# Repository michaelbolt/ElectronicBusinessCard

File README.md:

# ElectronicBusinessCard
This repository contains the code and PCB design files I developed for my Electronic Business Card project. To see writeups and follow my progress, follow my blog: [Mr. Dr. Prof. Bolt](https://mrdrprofbolt.wordpress.com/).

### Current State of the Project: Finished!
The MSP430FR2433 microcontroller communicates with the SSD1306 OLED display through I2C and handles 8x8 sprite-based animations. A Python GUI is available to help with creating animated sprite data. GPIO Port 2 is debounced using a polling algorithm for player input. A basic game loop implementing player controls (verical movement and lasers), enemy AI (vertical/horizontal movement and lasers), and collision detection (explosions!) is run at 16 Hz using the TimerA module and Low-Power Mode 3. Three different enemies are implemented along with collision detection and a score counter, with life-time high score stored in non-volatile FRAM. If the player gets a high score, a fireworks show is shown to celebrate!

### Using the Sprite Maker GUI
1. Download the `SpriteMaker.py` file from the `PythonScripts` folder.
2. Navigte to the directory where the source file is located. Use `cd [folder name]` to navigate on Mac/Linux or `DIR [folder name]` to navigate on Windows.
3. Run the script from the command line as `python SpriteMaker.py`. If you would like to see command line options, add the `-h` option.
4. Enjoy!

### Using the SSD1306 display functions
1. At the start of each frame, call `display_frameStart()`; this erases anything drawn on the last frame from VRAM.
2. Draw up to 16 sprites at (x,y) coordinates with `display_drawSprite(uint16_t x, uint16_t y, const uint8_t *const sprite)`.
3. After drawing all sprites, call `display_drawFrame()`; this updates all changed regions of the SSD1306 display with minimal I2C communication.

### Board Design files
Open in Eagle, edit the silkscreen to show your name, and go forth! Impress job interviewers, your friends, and anybody sitting next to you while waiting for a table at a restaurant!

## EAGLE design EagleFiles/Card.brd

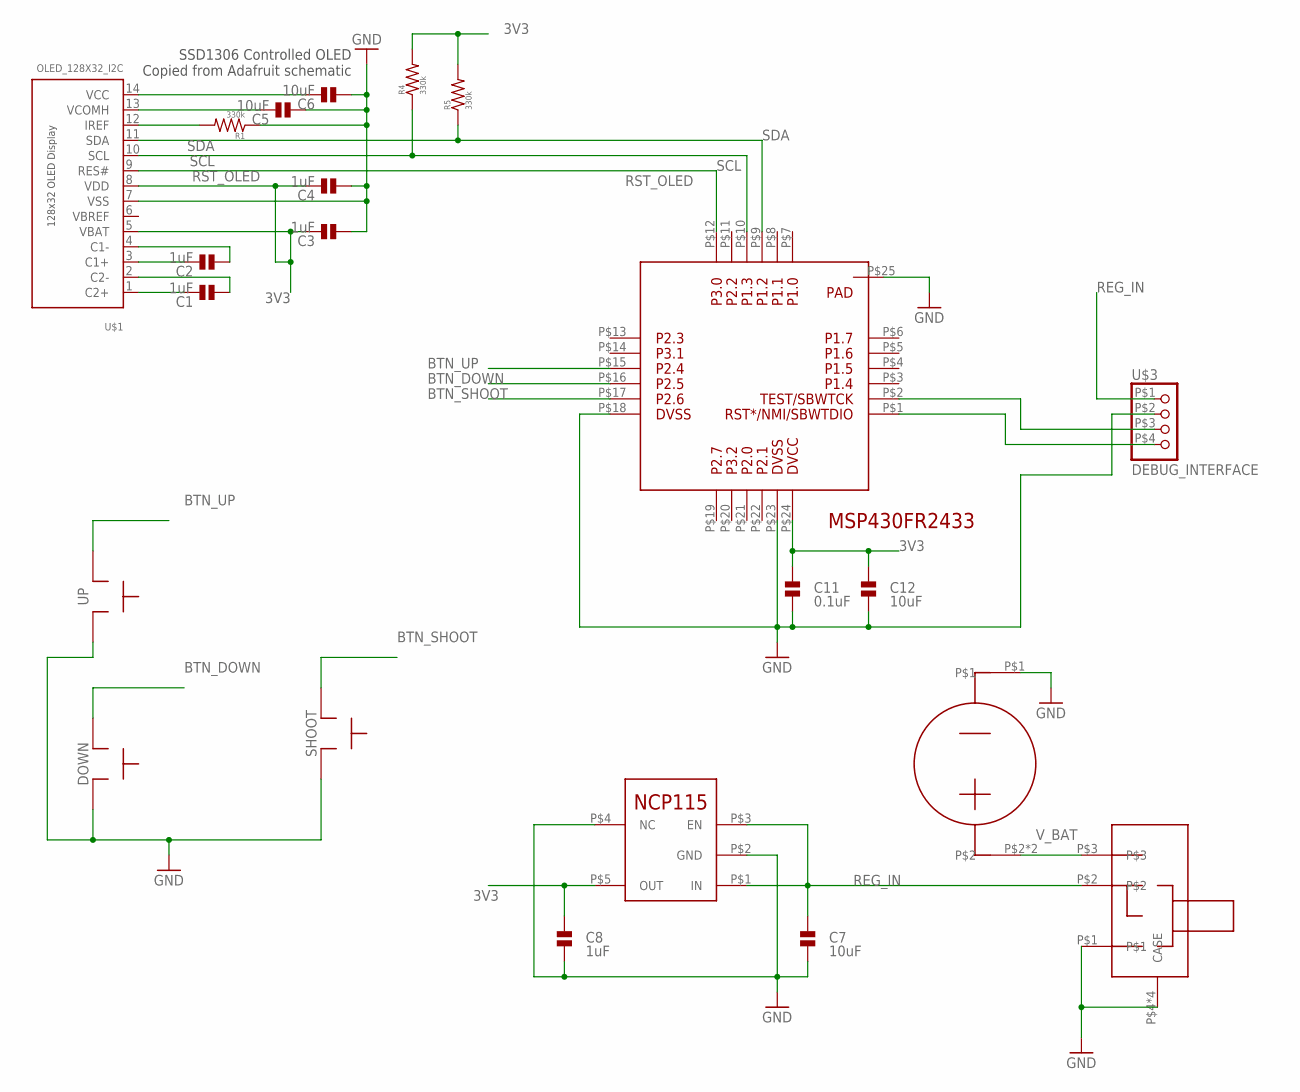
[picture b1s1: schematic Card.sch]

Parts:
C1, C2, C3, C4, C8: 1uF; 0603
C5, C6, C7, C12: 10uF; 0603
C11: 0.1uF; 0603
DOWN: EVQ-Q2B02W; EVQQ2
R1, R4, R5: 330k; 0603
SHOOT: EVQ-Q2B02W; EVQQ2
U$1: OLED_128X32_I2C; OLED_I2C
U$2: MSP430FR2433-VQFN; VQFN-24
U$3: DEBUG_INTERFACE; DEBUG_INTERFACE_6PIN
U$4: BAT-HLD-001
U$5: CUS-12TB; CUS-12B
U$6: NCP115; TSOP-5
UP: EVQ-Q2B02W; EVQQ2

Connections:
3V3: C3.2, C4.2, C8.2, C11.2, C12.2, R4.2, R5.2, U$1.5 (VBAT), U$1.8 (VDD), U$2.P$24, U$6.P$5 (OUT)
BTN_DOWN: DOWN.P$1_A, DOWN.P$2_A, U$2.P$16
BTN_SHOOT: SHOOT.P$1_A, SHOOT.P$2_A, U$2.P$17
BTN_UP: U$2.P$15, UP.P$1_A, UP.P$2_A
GND: C3.1, C4.1, C5.1, C6.1, C7.1, C8.1, C11.1, C12.1, DOWN.P$3_B, DOWN.P$4_B, R1.1, SHOOT.P$3_B, SHOOT.P$4_B, U$1.7 (VSS), U$2.P$18, U$2.P$23, U$2.P$25, U$3.P$2, U$4.P$1, U$5.P$1, U$5.P$4 (CASE), U$5.P$5 (CASE), U$5.P$6 (CASE), U$5.P$7 (CASE), U$6.P$2 (GND), U$6.P$4 (NC), UP.P$3_B, UP.P$4_B
unnamed: C1.2, U$1.1 (C2+)
unnamed: C1.1, U$1.2 (C2-)
unnamed: C2.2, U$1.3 (C1+)
unnamed: C2.1, U$1.4 (C1-)
unnamed: U$2.P$2, U$3.P$3
unnamed: U$2.P$1, U$3.P$4
unnamed: R1.2, U$1.12 (IREF)
unnamed: C5.2, U$1.13 (VCOMH)
unnamed: C6.2, U$1.14 (VCC)
REG_IN: C7.2, U$3.P$1, U$5.P$2, U$6.P$1 (IN), U$6.P$3 (EN)
RST_OLED: U$1.9 (RES#), U$2.P$12
SCL: R4.1, U$1.10 (SCL), U$2.P$10
SDA: R5.1, U$1.11 (SDA), U$2.P$9
VBREF: U$1.6 (VBREF)
V_BAT: U$4.P$2, U$4.P$3, U$5.P$3

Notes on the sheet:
SSD1306 Controlled OLED Copied from Adafruit schematic

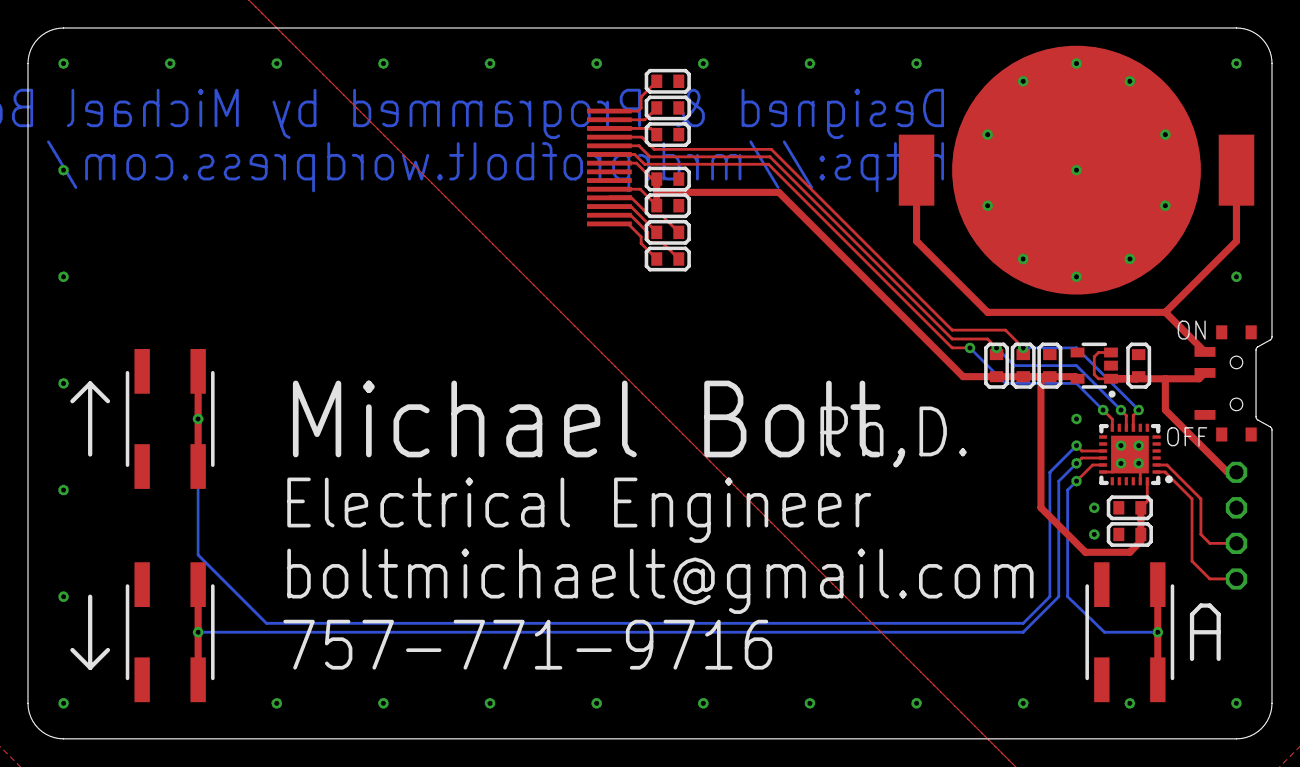
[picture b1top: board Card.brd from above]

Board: 2 copper layers, 88.9 x 50.8 mm, 22 parts (0 on the bottom side), 19 nets.

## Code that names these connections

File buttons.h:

/*
 * buttons.h
 *
 *  Created on: May 4, 2020
 *      Author: Michael Bolt
 */

#ifndef BUTTONS_H_
#define BUTTONS_H_


#include <msp430.h>
#include <stdint.h>

// button definitions
#define BTN_UP      BIT2
#define BTN_DOWN    BIT1
#define BTN_SHOOT   BIT0

// functions
void buttons_init(void);
inline uint16_t readButton(uint16_t button);


#endif /* BUTTONS_H_ */

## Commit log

2020-04-08 Created basic i2c initialization and transmission functions. TODO: test i2c functions with hardware
2020-04-09 Created SSD1306.h/.c to initialize and draw single pixel to OLED display. TODO: implement on-chip VRAM to allow multiple pixels in the same page to be drawn
2020-04-09 Implemented on-chip VRAM for SSD1306 drawing.
2020-04-15 VRAM drawing: pattern, triangle, and smiley face
2020-04-17 Added ssd1306_drawSprite() to draw 8x8 sprites.
2020-04-19 Python GUI to generate/animate sprite data.
2020-04-19 Fixed bug where changing spriteName would mess up code output.
2020-04-20 Implemented simple circular buffer for Dirty Rect Animation
2020-04-20 Implemented Dirty Rect animation - 'contrail' visible
2020-04-21 Final sprite display functions; implemented dirty rect merge
2020-04-21 Updated README.md for Blog post 3 - Animation
2020-05-01 Edge-triggered button ISR on P2.0 (demonstrates bouncing)
2020-05-04 Port-wide 40ms debounce implemented.
2020-05-04 Created buttons.h/c to provide button debouncing/reading.
2020-05-13 -Implemented 16 Hz timer for constant frame rate -Changed buttons.h/c to hardware.h/c
2020-05-13 Implemented 2 side-by-side player controller options
2020-05-13 Moved playerController() to game.h and sprites to gameSprites.c
2020-05-14 Cleaned game.h/c, made main loop more clear
2020-05-14 Updated README for blog 5
2020-05-19 Implemented enemy movements
2020-05-20 Added Ace Pilot lasers
2020-05-20 Enemy ships now explode when shot.
2020-05-20 Implemented score display
2020-05-21 Blog 6 - Enemy AI, Collisions, and Score
2020-09-27 Player Life sprite
2020-09-27 Sped up cloc to 16 MHz to draw lives
2020-09-27 Game is compelte, except for high score!
2020-09-27 Draws high score, game over freezes
2020-10-12 GameOver handling
    - added PRBS-11 pseudo-random number generator
    - if the player has a new high score, an animation of fireworks will be displayed.
2020-10-12 Finished the game!
    - Added FRAM high score storage
    - Put gameover logic inside infinite main loop
    - enemies are now generated with random periods in random order
2020-10-24 Added Board files
    Added Eagle component library and Business Cared schematic/board files
2020-10-24 Adding Documentation
    Added relevant datasheets and system pinout documents
2020-10-24 Final Code Cleaning
    Going through the code one more time to add clarification and comments
2020-11-28 Final README update
